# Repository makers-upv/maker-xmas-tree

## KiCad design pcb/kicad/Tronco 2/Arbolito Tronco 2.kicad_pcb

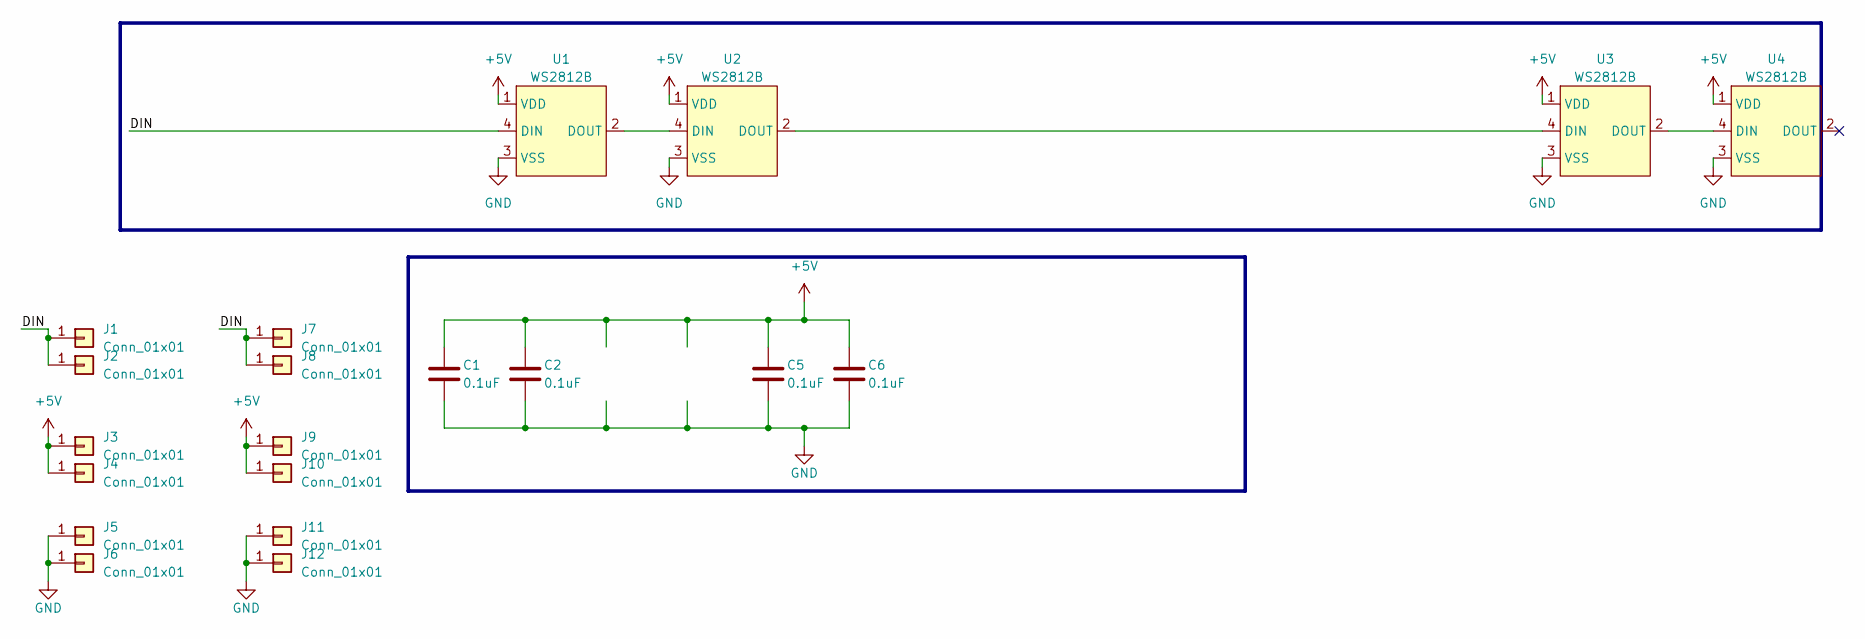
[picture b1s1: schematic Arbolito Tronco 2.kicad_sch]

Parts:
C1, C2, C5, C6: 0.1uF; C_0805_2012Metric
J1, J2, J3, J4, J5, J6, J7, J8, J9, J10, J11, J12: Conn_01x01; Output
U1, U2, U3, U4: WS2812B; LED_WS2812B_PLCC4_5.0x5.0mm_P3.2mm

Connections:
+5V: C1.1, C2.1, C5.1, C6.1, J3.1, J4.1, J9.1, J10.1, U1.1 (VDD), U2.1 (VDD), U3.1 (VDD), U4.1 (VDD)
/DIN: J1.1, J2.1, J7.1, J8.1, U1.4 (DIN)
GND: C1.2, C2.2, C5.2, C6.2, J5.1, J6.1, J11.1, J12.1, U1.3 (VSS), U2.3 (VSS), U3.3 (VSS), U4.3 (VSS)
unnamed: U1.2 (DOUT), U2.4 (DIN)
unnamed: U2.2 (DOUT), U3.4 (DIN)
unnamed: U3.2 (DOUT), U4.4 (DIN)

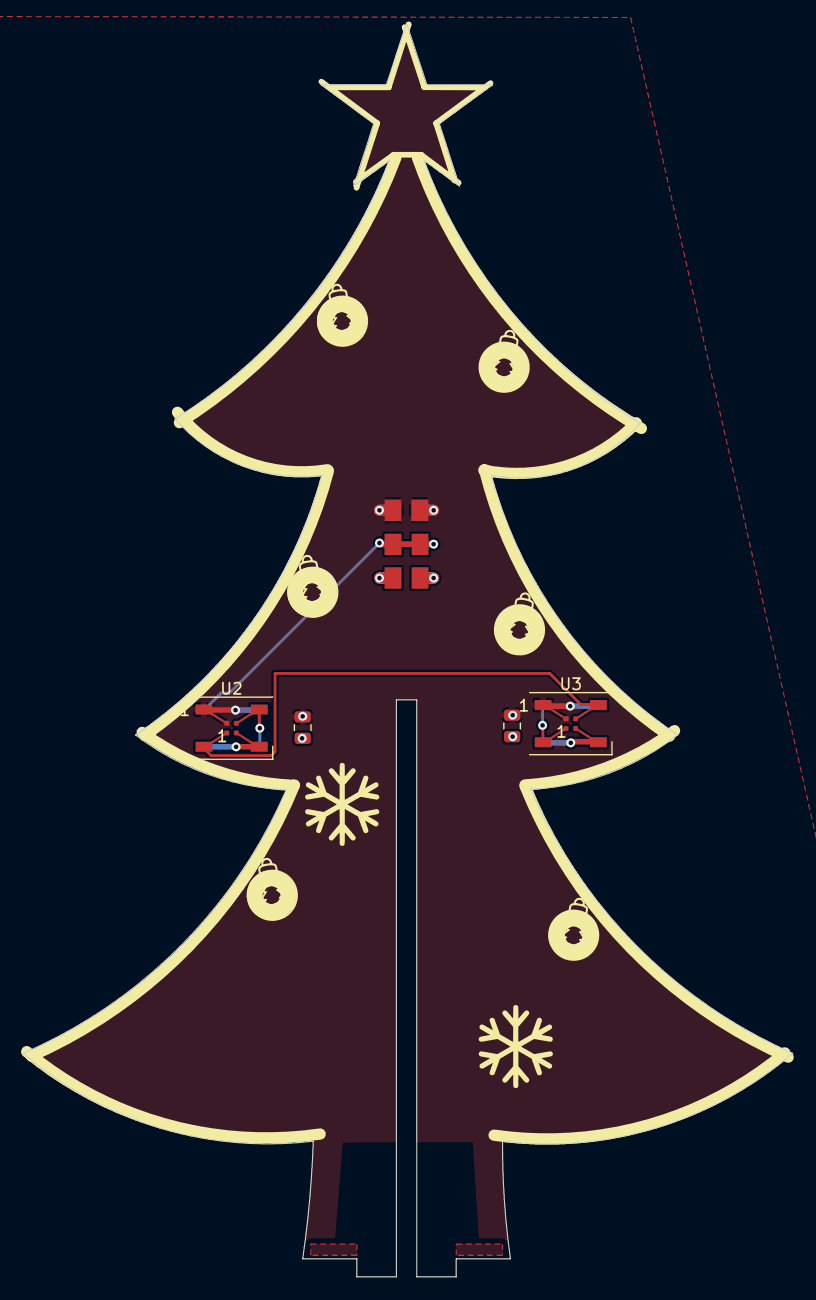
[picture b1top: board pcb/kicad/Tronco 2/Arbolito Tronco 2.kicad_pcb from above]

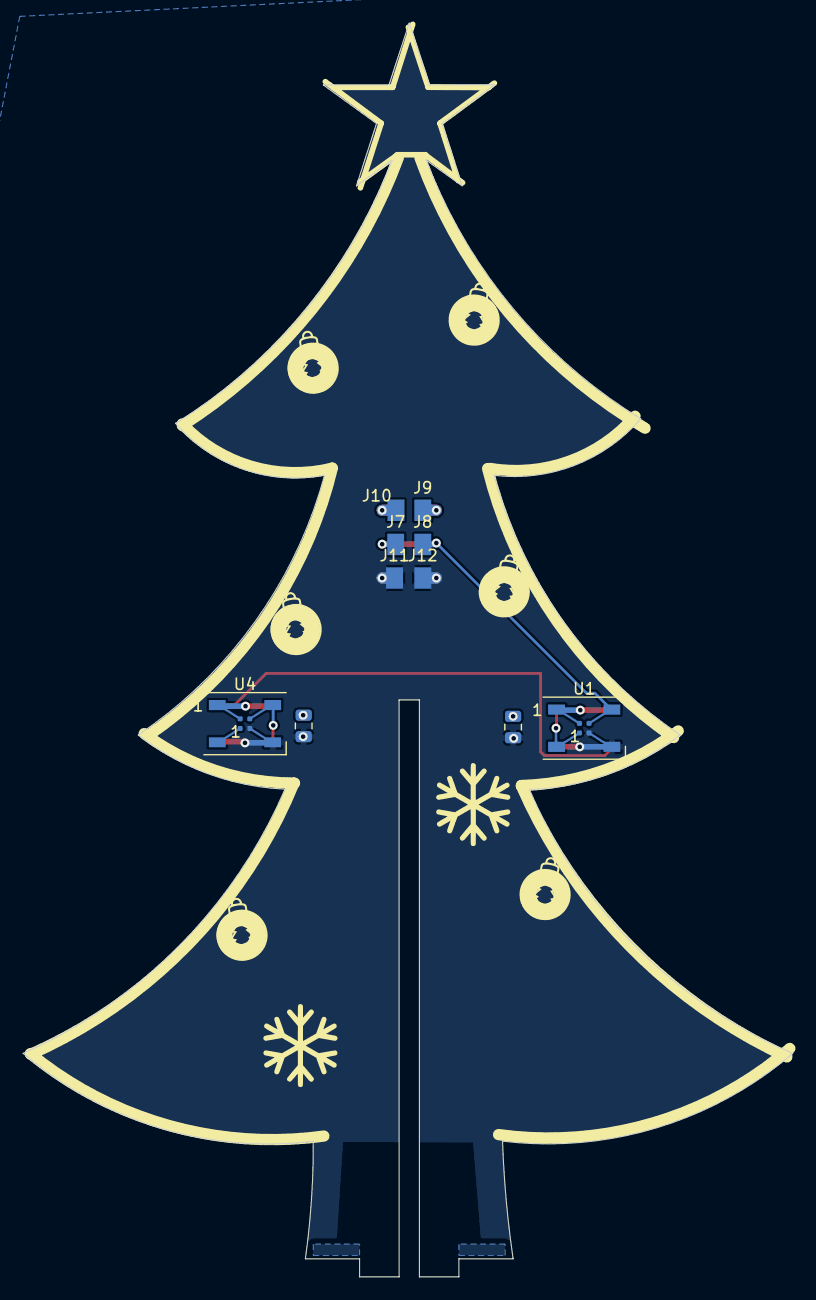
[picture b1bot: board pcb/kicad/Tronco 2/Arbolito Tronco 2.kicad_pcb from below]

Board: 2 copper layers, 68.2 x 111.0 mm, 20 parts (10 on the bottom side), 6 nets.

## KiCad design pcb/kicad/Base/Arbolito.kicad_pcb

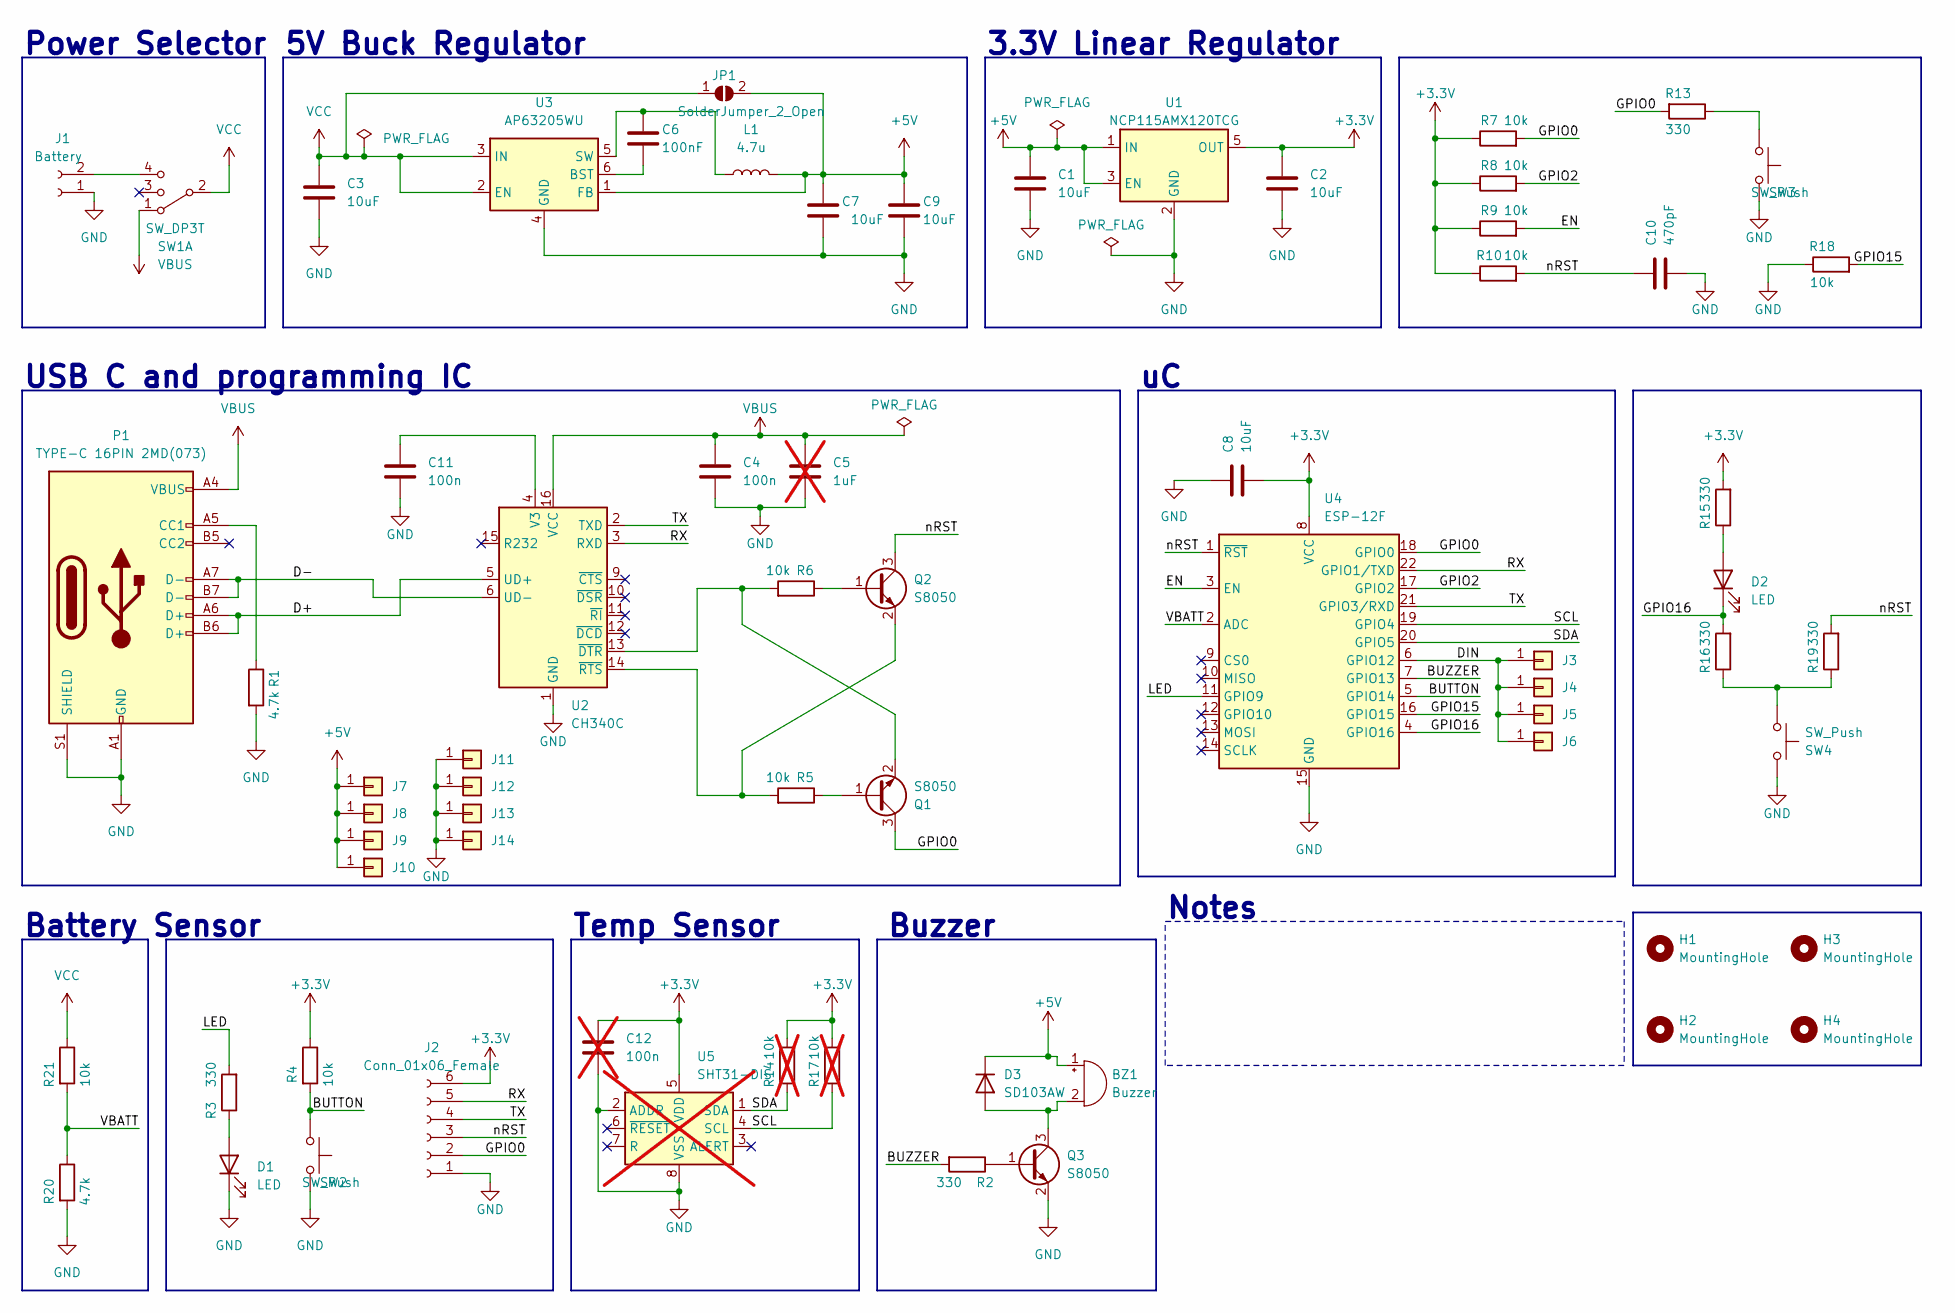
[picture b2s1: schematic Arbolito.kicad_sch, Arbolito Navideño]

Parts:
BZ1: Buzzer
C1, C2, C3, C7, C8, C9: 10uF; C_0805_2012Metric
C4, C11: 100n; C_0805_2012Metric
C5: 1uF; C_0805_2012Metric; not fitted
C6: 100nF; C_0805_2012Metric
C10: 470pF; C_0805_2012Metric
C12: 100n; C_0805_2012Metric; not fitted
D1, D2: LED; LED_0805_2012Metric
D3: SD103AW; D_SOD-123
H1, H2, H3, H4: MountingHole; MountingHole_3.2mm_M3_ISO7380
J1: Battery
J2: Conn_01x06_Female; PinHeader_1x06_P2.54mm_Vertical
J3, J4, J5, J6: Conn_01x01; Pad_tree_Data
J7, J8, J9, J10, J11, J12, J13, J14: Conn_01x01; Pad_tree_PS
JP1: SolderJumper_2_Open; SolderJumper-2_P1.3mm_Open_RoundedPad1.0x1.5mm
L1: 4.7u; L_Taiyo-Yuden_MD-3030
P1: TYPE-C 16PIN 2MD(073)
Q1, Q2, Q3: S8050; SOT-23
R1, R20: 4.7k; R_0805_2012Metric_Pad1.20x1.40mm_HandSolder
R2, R3, R13, R15, R16, R19: 330; R_0805_2012Metric_Pad1.20x1.40mm_HandSolder
R4, R5, R6, R7, R8, R9, R10, R18, R21: 10k; R_0805_2012Metric_Pad1.20x1.40mm_HandSolder
R14, R17: 10k; R_0805_2012Metric_Pad1.20x1.40mm_HandSolder; not fitted
SW1: SW_DP3T; 3PSwitch_Cheap
SW2, SW3, SW4: SW_Push; Button
U1: NCP115AMX120TCG; SOT-23-5_HandSoldering
U2: CH340C; SOIC-16_3.9x9.9mm_P1.27mm
U3: AP63205WU; TSOT-23-6
U4: ESP-12F; ESP-12E
U5: SHT31-DIS; Sensirion_DFN-8-1EP_2.5x2.5mm_P0.5mm_EP1.1x1.7mm; not fitted

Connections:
+5V: BZ1.1 (-), C1.1, C7.1, C9.1, D3.1 (K), J7.1, J8.1, J9.1, J10.1, JP1.2 (B), L1.2, U1.1 (IN), U1.3 (EN), U3.1 (FB)
/BUTTON: R4.2, SW2.1, U4.5 (GPIO14)
/BUZZER: R2.2, U4.7 (GPIO13)
/D+: P1.A6 (D+), P1.B6 (D+), U2.5 (UD+)
/D-: P1.A7 (D-), P1.B7 (D-), U2.6 (UD-)
/DIN: J3.1, J4.1, J5.1, J6.1, U4.6 (GPIO12)
/EN: R9.2, U4.3 (EN)
/GPIO0: J2.2, Q1.3 (C), R7.2, R13.2, U4.18 (GPIO0)
/GPIO2: R8.2, U4.17 (GPIO2)
/GPIO15: R18.2, U4.16 (GPIO15)
/GPIO16: D2.1 (K), R16.2, U4.4 (GPIO16)
/LED: R3.2, U4.11 (GPIO9)
/RX: J2.5, U2.3 (RXD), U4.22 (GPIO1/TXD)
/SCL: R17.1, U4.19 (GPIO4), U5.4 (SCL)
/SDA: R14.1, U4.20 (GPIO5), U5.1 (SDA)
/TX: J2.4, U2.2 (TXD), U4.21 (GPIO3/RXD)
/VBATT: R20.1, R21.2, U4.2 (ADC)
/nRST: C10.1, J2.3, Q2.3 (C), R10.2, R19.2, U4.1 (~RST)
unnamed: BZ1.2 (+), D3.2 (A), Q3.3 (C)
unnamed: D1.2 (A), R3.1
unnamed: D2.2 (A), R15.1
unnamed: J1.2, SW1.4
unnamed: P1.A5 (CC1), R1.1
unnamed: Q1.1 (B), R5.1
unnamed: Q1.2 (E), R6.2, U2.13 (~DTR)
unnamed: Q2.1 (B), R6.1
unnamed: Q2.2 (E), R5.2, U2.14 (~RTS)
unnamed: Q3.1 (B), R2.1
unnamed: R13.1, SW3.1
unnamed: R16.1, R19.1, SW4.1
unnamed: C11.1, U2.4 (V3)
unnamed: C6.2, U3.6 (BST)
unnamed: C6.1, L1.1, U3.5 (SW)
VBUS: C4.1, C5.1, P1.A4 (VBUS), P1.A9 (VBUS), P1.B4 (VBUS), P1.B9 (VBUS), SW1.1, U2.16 (VCC)
VCC: C3.1, JP1.1 (A), R21.1, SW1.2 (1), U3.2 (EN), U3.3 (IN)

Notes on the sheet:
Power Selector
Temp Sensor
Buzzer
USB C and programming IC
3.3V Linear Regulator
Battery Sensor
5V Buck Regulator
Notes

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
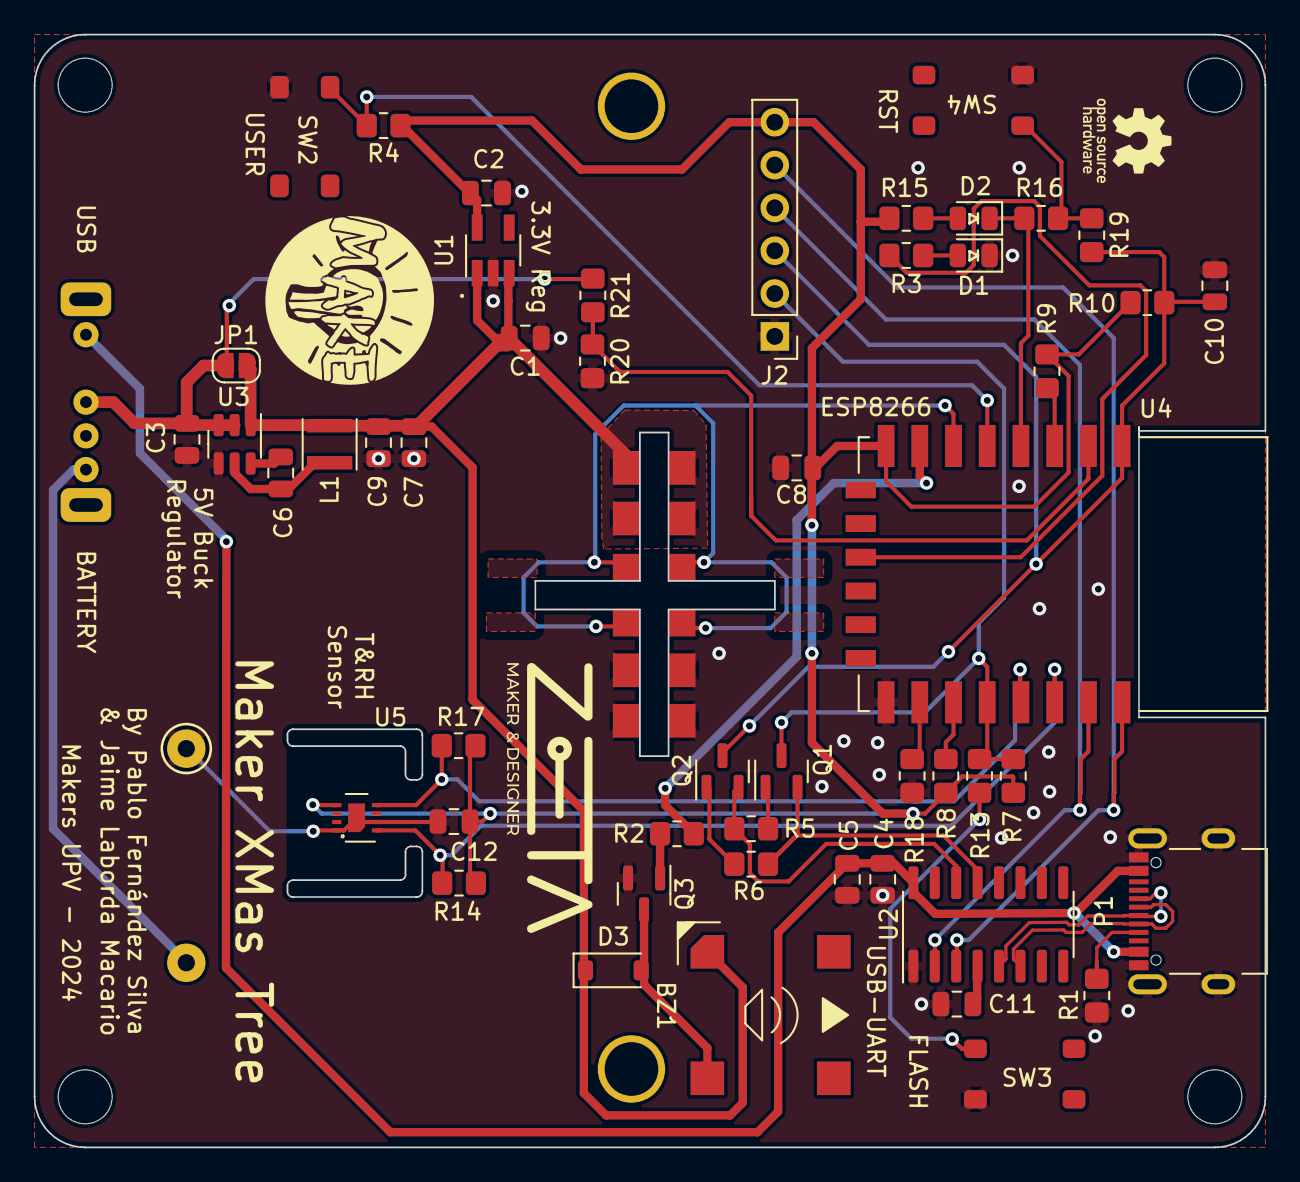
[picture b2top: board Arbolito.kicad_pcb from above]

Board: 2 copper layers, 73.0 x 66.0 mm, 68 parts (1 on the bottom side), 37 nets.

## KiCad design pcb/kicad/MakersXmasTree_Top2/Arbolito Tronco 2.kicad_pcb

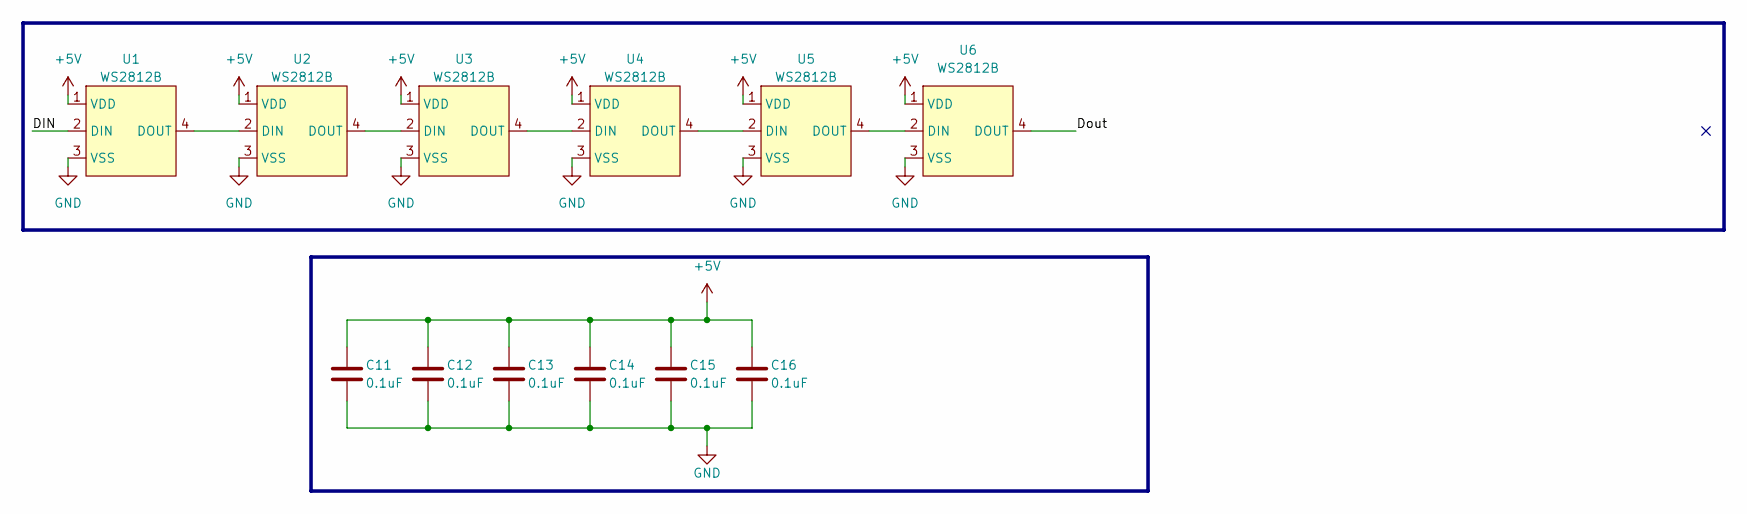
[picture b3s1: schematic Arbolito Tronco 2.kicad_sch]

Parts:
C11, C12, C13, C14, C15, C16: 0.1uF; C_0805_2012Metric
U1, U2, U3, U4, U5, U6: WS2812B; LED_WS2812B_PLCC4_5.0x5.0mm_P3.2mm

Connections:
+5V: C11.1, C12.1, C13.1, C14.1, C15.1, C16.1, U1.1 (VDD), U2.1 (VDD), U3.1 (VDD), U4.1 (VDD), U5.1 (VDD), U6.1 (VDD)
/DIN: U1.2 (DIN)
/Dout: U6.4 (DOUT)
GND: C11.2, C12.2, C13.2, C14.2, C15.2, C16.2, U1.3 (VSS), U2.3 (VSS), U3.3 (VSS), U4.3 (VSS), U5.3 (VSS), U6.3 (VSS)
unnamed: U1.4 (DOUT), U2.2 (DIN)
unnamed: U2.4 (DOUT), U3.2 (DIN)
unnamed: U3.4 (DOUT), U4.2 (DIN)
unnamed: U4.4 (DOUT), U5.2 (DIN)
unnamed: U5.4 (DOUT), U6.2 (DIN)

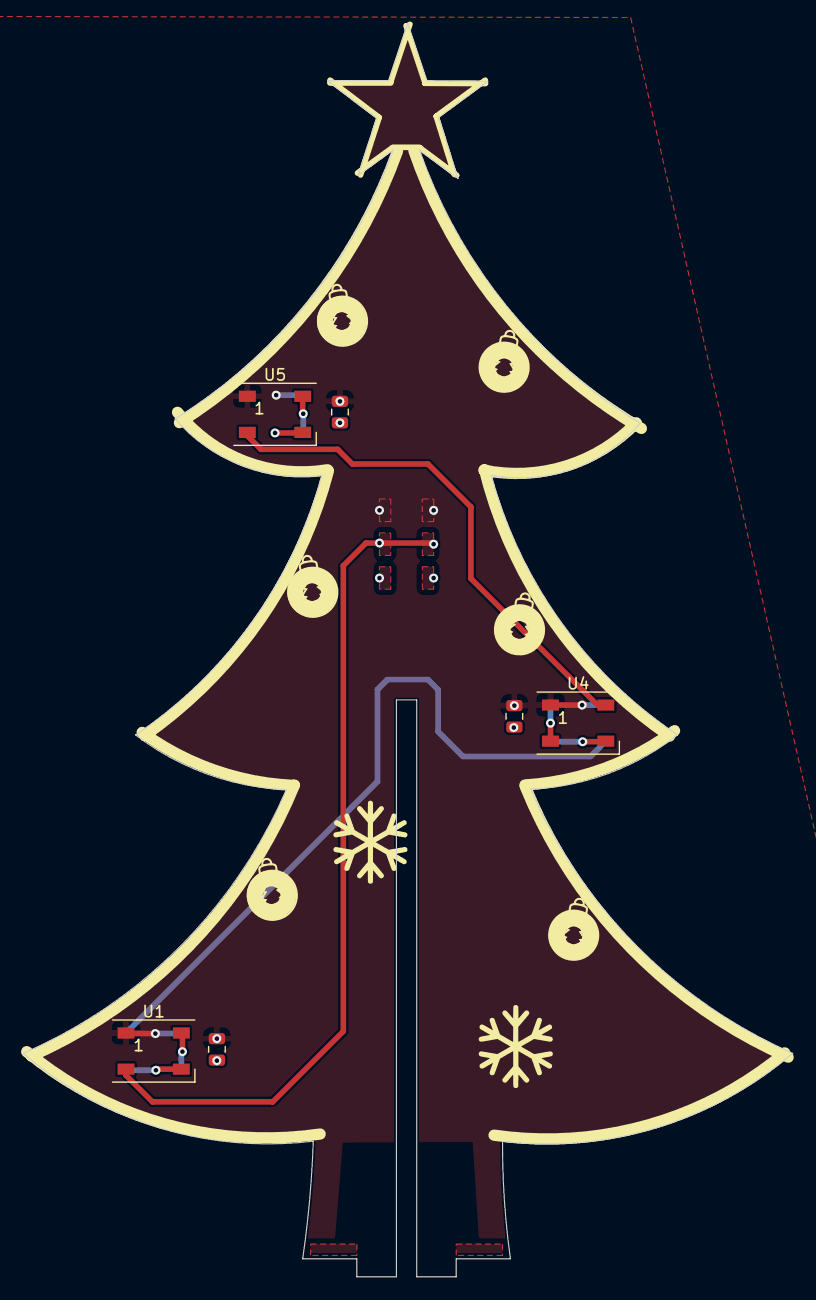
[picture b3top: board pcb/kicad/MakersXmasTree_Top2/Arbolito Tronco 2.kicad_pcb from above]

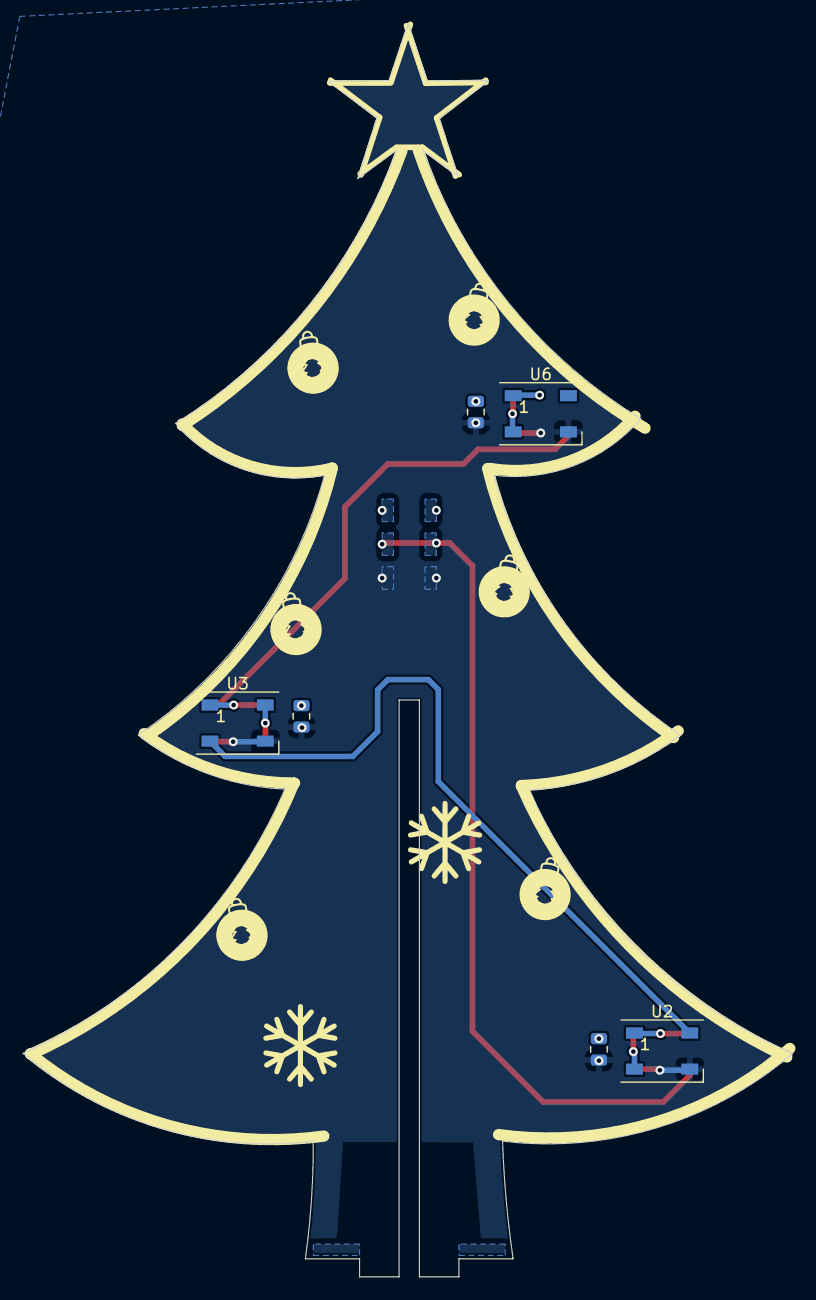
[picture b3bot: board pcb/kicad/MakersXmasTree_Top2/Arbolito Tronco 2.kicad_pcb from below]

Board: 2 copper layers, 68.2 x 111.0 mm, 12 parts (6 on the bottom side), 7 nets.

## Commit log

2022-12-11 Added PCB kicad source code and documentation
2022-12-11 Added example index.html to test web for redirect to interactive bom
2022-12-11 Added Interactive BOM files to the web
2022-12-15 Change R20 with 1K resistor
2022-12-22 Add ESPHome .yaml and presentation
2023-10-28 CH340 VERSION
2023-11-01 New_Footprints
    3PSwitch and button footprints added to library. (not yet to PCB)
2023-11-01 SHT31 addition
    SHT11 Temp sensor changed to SHT31. Furthermore isolation slots where included
2023-11-03 Switch and buttons
    Switch and buttons changed on PCB
2023-11-03 Switchs Corrected
2023-11-09 Few leds version added
2023-11-10 Footprints corrected
2023-11-11 Modified USB C Molex 2169900002 footprint and added 3D step
2023-11-12 BatteryHolder on place :3
2023-11-12 Data lines fixed
2023-11-12 Pre USB change
2023-11-12 Led Footprint Changed
2023-11-12 Modified USB-C with 3 cents version
2023-11-12 Gerbers
2023-12-14 BomAdded
2023-12-16 Do some cleaning and add .gitignore
2023-12-17 Added Rev3 release files
    - Added ibom html files
    - Update ibom in .web directory
    - Update pdf schematics
    - Added 3D steps files
    - Added tools for help to mount the PCB
    - Added hw rev3 gerber files
2023-12-17 Revert "BomAdded"
    This reverts commit b7ee5e297438f619dc395325b34e48b47fd152b4.
2023-12-20 Modify ibom html and added WLED binary files
2024-08-25 USB Issues fixed
    USB C Now reversible
    USB C progamable
2024-08-25 Led Shorts fixed
    Vias were shorting leds pins, should be fixed :)
2024-08-26 DRC Errors fixeds
    The WS218B double footprint was remade in order to avoid DRC errors :3
